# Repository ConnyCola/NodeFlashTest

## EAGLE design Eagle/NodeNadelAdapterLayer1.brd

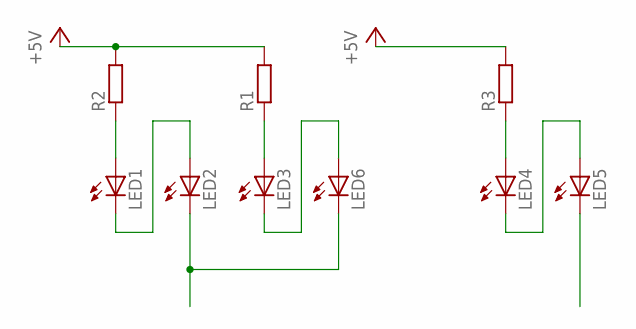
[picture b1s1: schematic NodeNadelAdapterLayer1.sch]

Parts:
LED1, LED2, LED3, LED4, LED5, LED6: LEDSML0805; SML0805
R1, R2, R3: R-EU_R0603; R0603

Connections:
+5V: R1.2, R2.2, R3.2
unnamed: LED2.C, LED6.C
unnamed: LED1.A, R2.1
unnamed: LED1.C, LED2.A
unnamed: LED3.C, LED6.A
unnamed: LED3.A, R1.1
unnamed: LED4.A, R3.1
unnamed: LED4.C, LED5.A

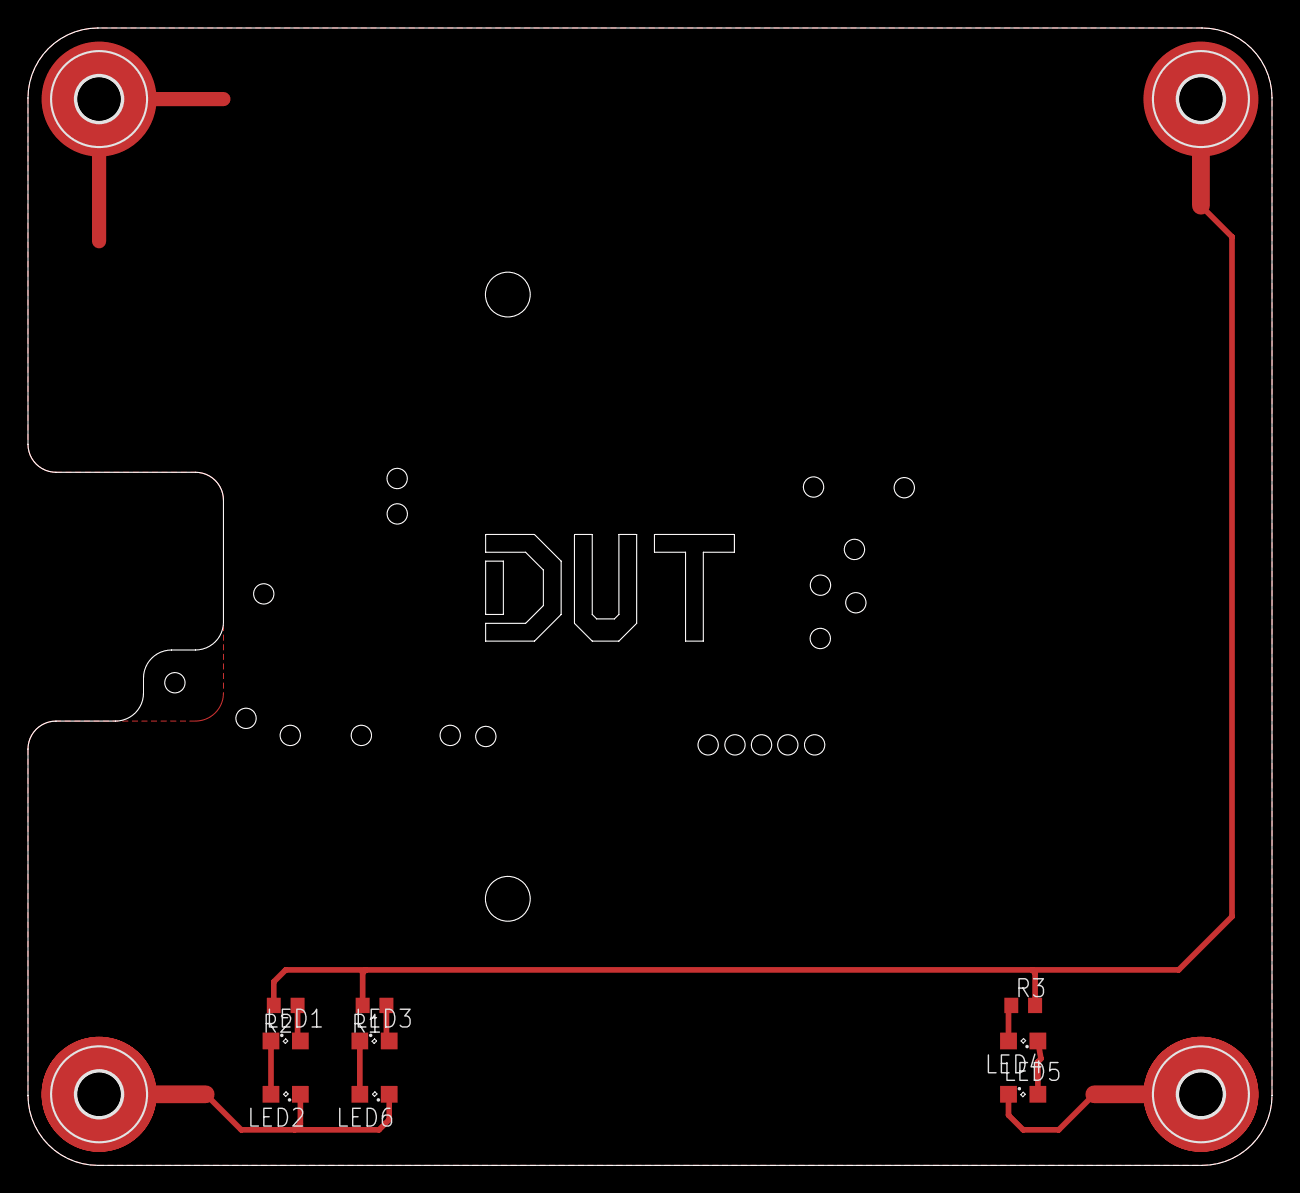
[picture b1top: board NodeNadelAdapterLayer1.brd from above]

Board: 2 copper layers, 88.9 x 81.3 mm, 13 parts (0 on the bottom side), 8 nets.

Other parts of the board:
H1, H2, H3, H4: MOUNT-HOLE3.2; 3,2

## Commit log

2015-03-25 first push
    Flash and test tool for MSP430
